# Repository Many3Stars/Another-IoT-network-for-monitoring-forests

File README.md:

# IoT Monitoring System for Forest Environments

Author: Manuel Álvarez Herrera  
Supervisor: José Antonio García Souto  
Year: 2024

## Abstract

This project implements an IoT system to monitor forest environments, particularly coniferous and oak forests, aiming to study the effects of climate change. The IoT network consists of sensor nodes, intermediate nodes, and a database, enabling the collection and analysis of environmental and tree health data.

## Objectives

The primary objective is to observe the impact of climate change on trees by collecting relevant data such as temperature, humidity, solar radiation, and other key indicators.

## Technologies Used

- **Hardware:** Arduino, Raspberry Pi, Dragino NBSN95, LSN50, temperature, humidity sensors, and more.
- **Communication Protocols:** LoRa, NB-IoT, WiFi.
- **Databases:** InfluxDB, ThingsBoard, Home Assistant.
- **Weather Stations:** Ecowitt, Wunderground, Weathercloud.

## IoT Network Structure

1. **Sensor Node A:** Arduino Uno, Raspberry Pi 4 B, sensors for foliage and soil.
2. **Sensor Node B:** Dragino NBSN95 and LSN50 devices.
3. **Sensor Node C:** Sainlogic WS3500 weather station.

## Results

The system was successfully tested in a controlled environment, obtaining accurate data for forest environment analysis. The tests demonstrated the system's viability for monitoring remote forests.

## Conclusion

The designed IoT system is scalable, energy-efficient, and adaptable to various environments, including farms and urban forest areas.

## Repository

The code and additional documentation are available in the following GitHub repository:  
[Another IoT network for monitoring forests](https://github.com/Many3Stars/IoT-network-for-monitoring-forests)

## References

1. K. Raviteja, M. Supriya, "IoT-Based Agriculture Monitoring System", Springer, 2020.
2. N. Suma, S. Samson, "Recent Innovations in Computing and Communication", 2021.
3. Kazuho M., Takeshi O., "Dependence of Stomatal Conductance on Leaf Chlorophyll Concentration", 2025.

---

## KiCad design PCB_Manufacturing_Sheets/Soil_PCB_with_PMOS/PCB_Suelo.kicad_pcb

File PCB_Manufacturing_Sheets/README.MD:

# PCB Manufacturing Sheets

This folder contains all the necessary schematics and designs for the manufacturing of PCBs related to the data acquisition and power supply of soil and leaf sensors.

## Overview

The designs in this folder are intended to be used with KiCad for PCB design and fabrication. The PCBs are categorized into two primary functions:

- **Power Supply PCBs:** Provide the required voltage levels for sensors and associated circuits.
- **Datalog PCBs:** Handle data acquisition from sensors and ensure reliable data transmission to the Arduino for processing.

### Sensors Supported

1. **Soil Sensors:** Measure parameters like soil humidity, temperature, and pH.
2. **Leaf Sensors:** Measure parameters like leaf humidity, temperature, and stomatal temperature.

---

## Components and Design Highlights

### Key Components
- Voltage regulators for stable power supply.
- PMOS/NMOS transistors for energy-efficient activation/deactivation.
- Circuitry for data acquisition and sensor-specific power requirements.

### PMOS vs NMOS Switching
- **PMOS Design (Recommended):** Low leakage current in the "off" state, ensuring better energy efficiency.
- **NMOS Design:** Functional but with higher leakage current, making it less efficient for long-term applications.

---

## Folder Structure and Details

Each subfolder contains files for a specific PCB design:

### 1. **Power_Supply_PCB**
   - Contains the schematic and PCB layout for the power supply.
   - Includes voltage regulation and distribution for all components.

### 2. **Leaf_PCB_with_NMOS**
   - PCB design for leaf sensors using an NMOS transistor for switching.
   - Measures leaf-related parameters like humidity and temperature.

### 3. **Leaf_PCB_with_PMOS**
   - PCB design for leaf sensors using a PMOS transistor for switching.
   - Optimized for energy efficiency with minimal leakage current.

### 4. **Soil_PCB_with_NMOS**
   - PCB design for soil sensors using an NMOS transistor for switching.
   - Measures soil parameters like humidity, temperature, and pH.

### 5. **Soil_PCB_with_PMOS**
   - PCB design for soil sensors using a PMOS transistor for switching.
   - Designed for low-power consumption and long-term deployments.

---

## Design Recommendations

- **Use PMOS designs for both leaf and soil sensors** to minimize power consumption during standby periods.
- Ensure all components are compatible with the specific voltage and current requirements of your sensors.

---

## How to Use

1. Open the KiCad project files from the respective subfolders.
2. Verify the schematic and PCB design as per your requirements.
3. Export the Gerber files for manufacturing.
4. Assemble the PCB using the components listed in the schematic.

---

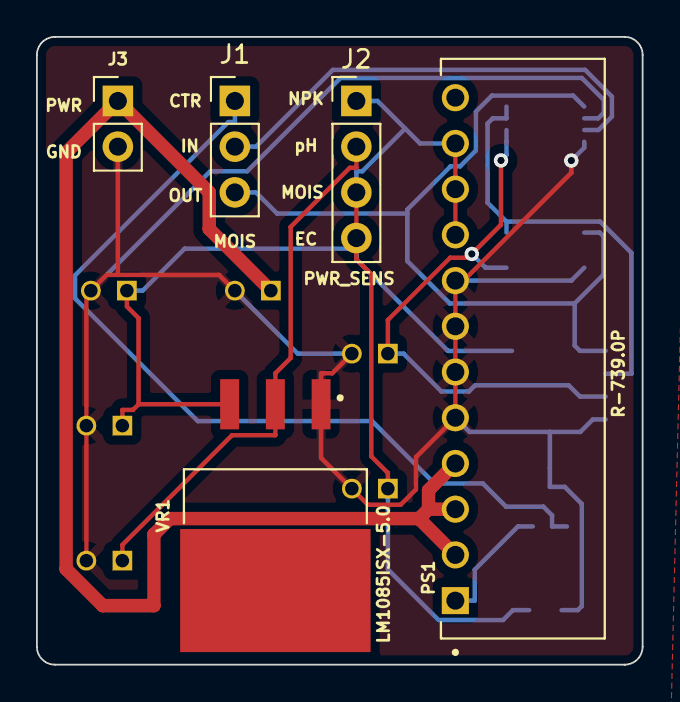
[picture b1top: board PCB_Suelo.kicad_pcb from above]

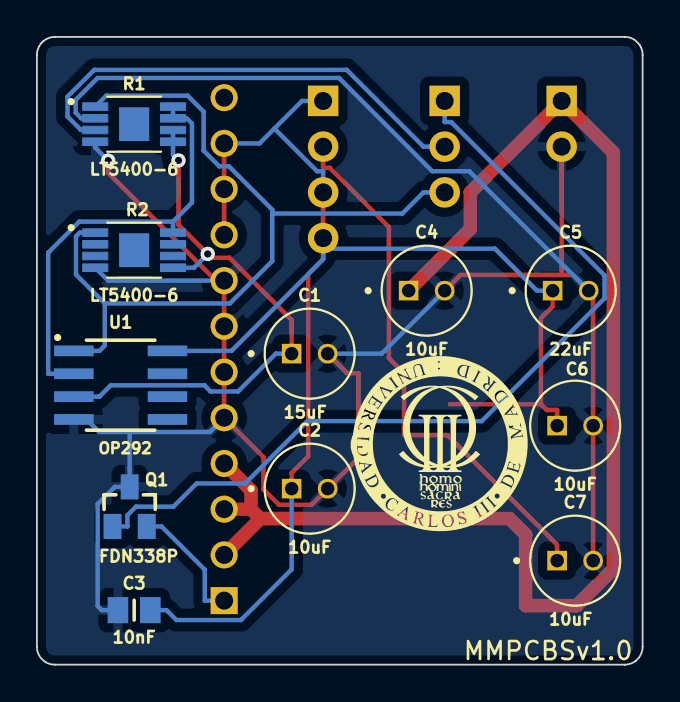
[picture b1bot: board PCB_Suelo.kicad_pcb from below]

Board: 2 copper layers, 33.7 x 34.9 mm, 17 parts (12 on the bottom side), 10 nets.

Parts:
C1, C2, C4, C5, C6, C7: EEUFC1H150; CAPPRD200W50D500H1100
C3: CL21B103KBANNNC; CAPC2012X140N
G: L; Logo2
J1: Conn_01x03; PinHeader_1x03_P2.54mm_Vertical
J2: Conn_01x04; PinHeader_1x04_P2.54mm_Vertical
J3: Conn_01x02; PinHeader_1x02_P2.54mm_Vertical
PS1: R-739.0P; CONV_R-739.0P
Q1: FDN338P; SSOT-3
R1, R2: LT5400BCMS8E-6#PBF; SOP65P490X110-9N
U1: OP292GSZ-REEL; SOIC127P600X175-8N
VR1: LM1085ISX-5.0/NOPB; TO254P1435X464-4N

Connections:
9V: C2.P, C3.2, C5.P, C6.P, J2.1, J2.3, J2.4, PS1.9 (VOUT), PS1.10 (VOUT), PS1.11 (VOUT), U1.8 (V+), VR1.3 (INPUT)
CTR: J1.1, Q1.1
GND: C1.N, C2.N, C3.1, C4.N, C5.N, C6.N, C7.N, J3.2, PS1.5 (GND), PS1.6 (GND), PS1.7 (GND), PS1.8 (GND), Q1.3, R1.2, R1.4, R2.4, U1.4 (V-), VR1.1 (ADJ/GND)
IN_MOISTURE: J1.2, R1.3
unnamed: C1.P, R1.5, R1.6, R2.5, U1.3 (+INA)
unnamed: PS1.1 (~ON/OFF), Q1.2
unnamed: R1.7, R1.8, R2.8, U1.2 (-INA)
OUT_MOISTURE: J1.3, R1.1, R2.1, U1.1 (OUTA)
PWR: C4.P, J3.1, PS1.2 (VIN), PS1.3 (VIN), PS1.4 (VIN)
PWR_pH: C7.P, J2.2, VR1.2 (OUTPUT_2)

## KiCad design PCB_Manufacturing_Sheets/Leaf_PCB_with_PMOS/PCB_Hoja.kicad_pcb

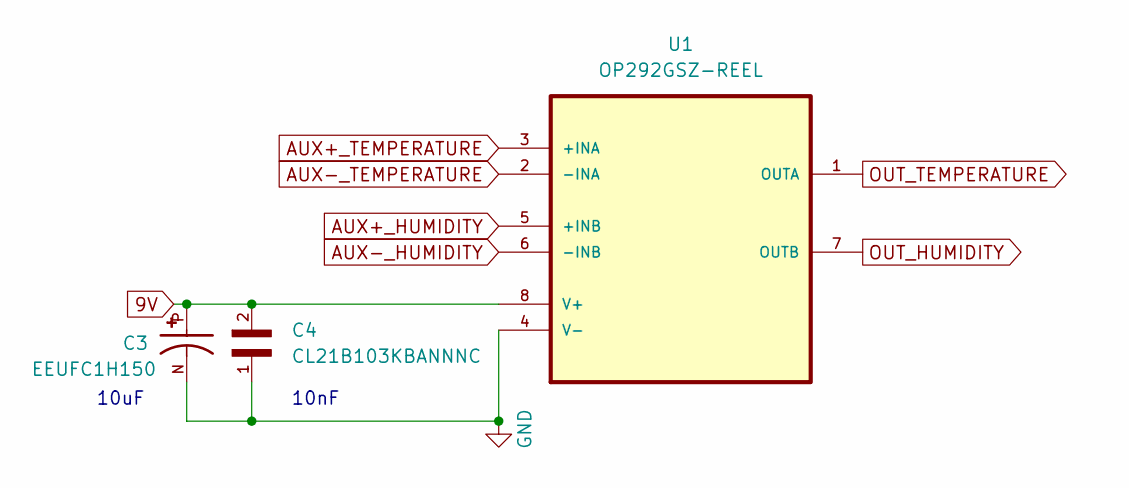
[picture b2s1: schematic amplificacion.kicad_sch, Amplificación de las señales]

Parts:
C3: EEUFC1H150; CAPPRD200W50D500H1100; PARTREV 20-DEC-19
C4: CL21B103KBANNNC; CAPC2012X140N
U1: OP292GSZ-REEL; SOIC127P600X175-8N; MPN OP292GSZ-REEL

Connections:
9V: C3.P, C4.2, U1.8 (V+); also elsewhere on the board
AUX+_HUMIDITY: U1.5 (+INB); also elsewhere on the board
AUX+_TEMPERATURE: U1.3 (+INA); also elsewhere on the board
AUX-_HUMIDITY: U1.6 (-INB); also elsewhere on the board
AUX-_TEMPERATURE: U1.2 (-INA); also elsewhere on the board
GND: C3.N, C4.1, U1.4 (V-); also elsewhere on the board
OUT_HUMIDITY: U1.7 (OUTB); also elsewhere on the board
OUT_TEMPERATURE: U1.1 (OUTA); also elsewhere on the board

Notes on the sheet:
10nF
10uF

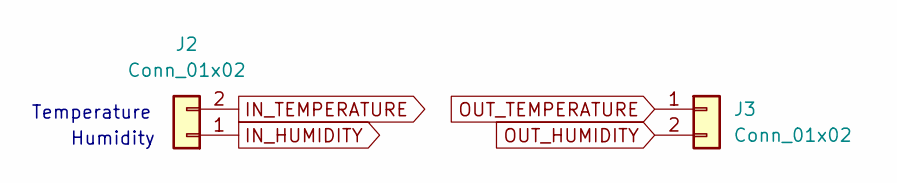
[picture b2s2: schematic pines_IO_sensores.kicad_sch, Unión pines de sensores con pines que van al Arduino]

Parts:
J2, J3: Conn_01x02; PinHeader_1x02_P2.54mm_Vertical

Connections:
IN_HUMIDITY: J2.1; also elsewhere on the board
IN_TEMPERATURE: J2.2; also elsewhere on the board
OUT_HUMIDITY: J3.2; also elsewhere on the board
OUT_TEMPERATURE: J3.1; also elsewhere on the board

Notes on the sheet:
Humidity
Temperature

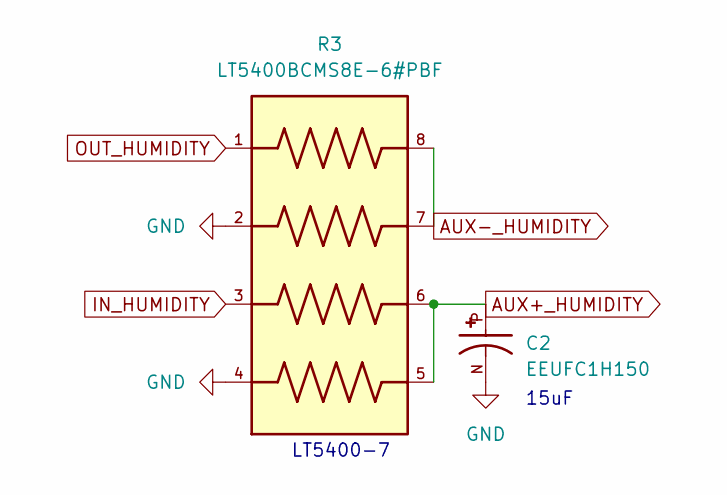
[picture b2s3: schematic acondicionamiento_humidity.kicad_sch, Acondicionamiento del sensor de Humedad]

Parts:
C2: EEUFC1H150; CAPPRD200W50D500H1100; PARTREV 20-DEC-19
R3: LT5400BCMS8E-6#PBF; SOP65P490X110-9N; PARTREV I

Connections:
AUX+_HUMIDITY: C2.P, R3.5, R3.6; also elsewhere on the board
AUX-_HUMIDITY: R3.7, R3.8; also elsewhere on the board
GND: C2.N, R3.2, R3.4; also elsewhere on the board
IN_HUMIDITY: R3.3; also elsewhere on the board
OUT_HUMIDITY: R3.1; also elsewhere on the board

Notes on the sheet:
LT5400-7
15uF

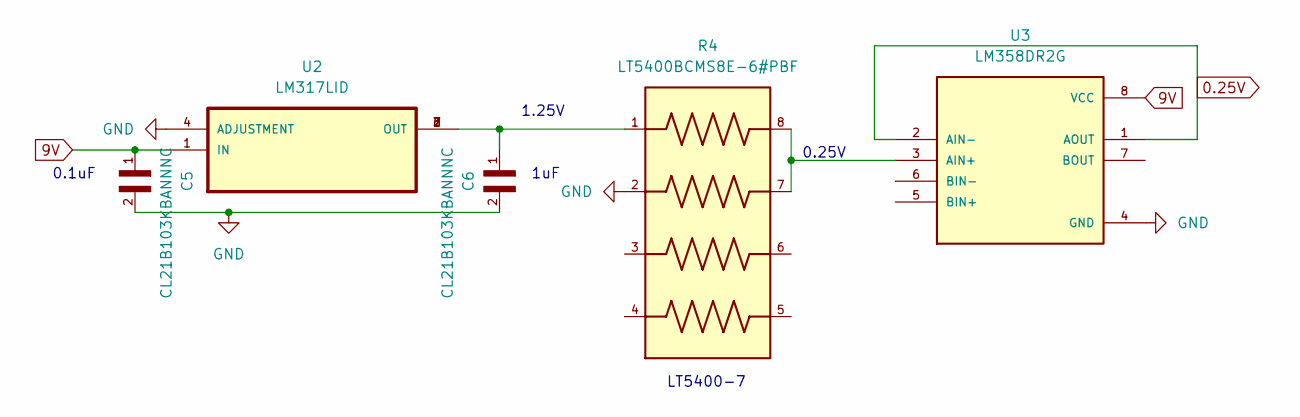
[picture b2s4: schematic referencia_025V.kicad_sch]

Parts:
C5, C6: CL21B103KBANNNC; CAPC2012X140N
R4: LT5400BCMS8E-6#PBF; SOP65P490X110-9N; PARTREV I
U2: LM317LID; SOIC127P599X175-8N
U3: LM358DR2G; SOIC127P600X175-8N

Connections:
0.25V: U3.1 (AOUT), U3.2 (AIN-); also elsewhere on the board
9V: C5.1, U2.1 (IN), U3.8 (VCC); also elsewhere on the board
GND: C5.2, C6.2, R4.2, U2.4 (ADJUSTMENT), U3.4 (GND); also elsewhere on the board
unnamed: C6.1, R4.1, U2.2 (OUT), U2.3 (OUT), U2.6 (OUT), U2.7 (OUT)
unnamed: R4.7, R4.8, U3.3 (AIN+)

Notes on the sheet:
1uF
0.25V
0.1uF
LT5400-7
1.25V

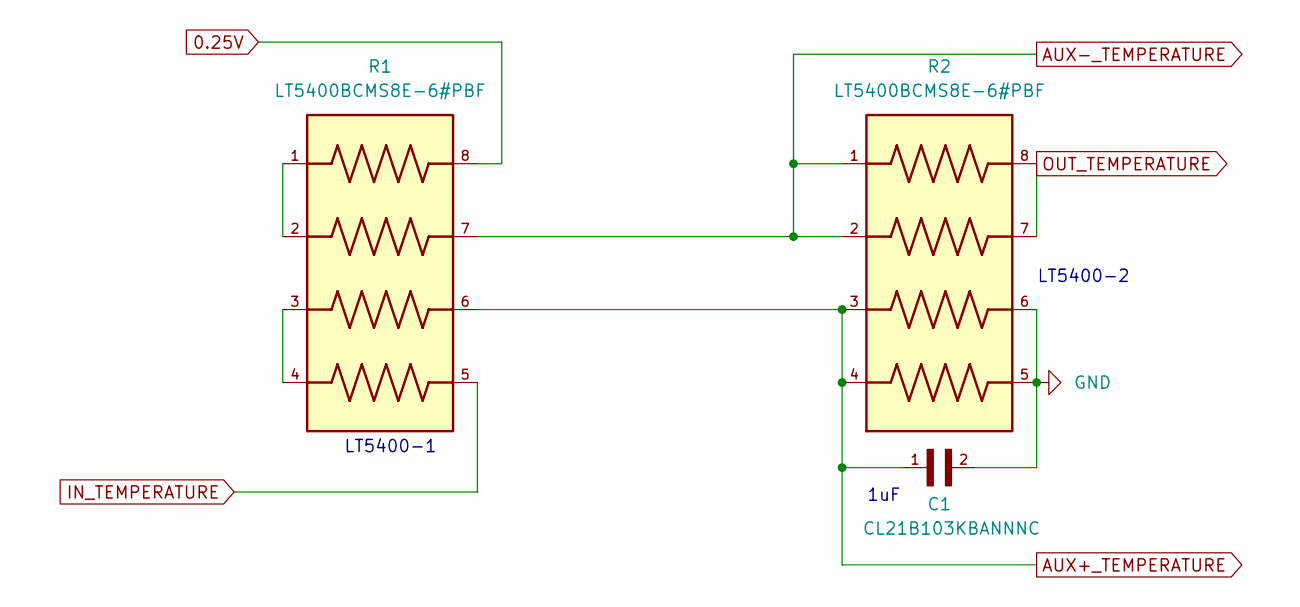
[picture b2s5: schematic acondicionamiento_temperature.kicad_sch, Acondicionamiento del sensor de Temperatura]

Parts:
C1: CL21B103KBANNNC; CAPC2012X140N
R1, R2: LT5400BCMS8E-6#PBF; SOP65P490X110-9N; PARTREV I

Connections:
0.25V: R1.8; also elsewhere on the board
AUX+_TEMPERATURE: C1.1, R1.6, R2.3, R2.4; also elsewhere on the board
AUX-_TEMPERATURE: R1.7, R2.1, R2.2; also elsewhere on the board
GND: C1.2, R2.5, R2.6; also elsewhere on the board
IN_TEMPERATURE: R1.5; also elsewhere on the board
unnamed: R1.1, R1.2
unnamed: R1.3, R1.4
OUT_TEMPERATURE: R2.7, R2.8; also elsewhere on the board

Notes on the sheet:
LT5400-2
LT5400-1
1uF

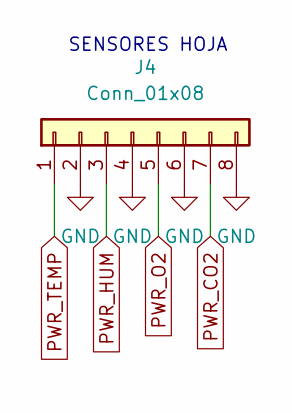
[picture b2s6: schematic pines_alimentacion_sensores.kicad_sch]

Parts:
J4: Conn_01x08; PinHeader_1x08_P2.54mm_Vertical

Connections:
GND: J4.2, J4.4, J4.6, J4.8; also elsewhere on the board
PWR_CO2: J4.3, J4.5, J4.7; also elsewhere on the board
PWR_TEMP: J4.1; also elsewhere on the board

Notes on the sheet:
SENSORES HOJA

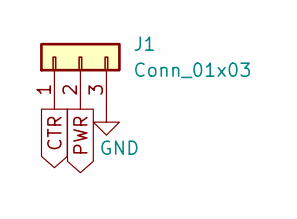
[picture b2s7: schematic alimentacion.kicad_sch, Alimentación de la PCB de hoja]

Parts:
J1: Conn_01x03; PinHeader_1x03_P2.54mm_Vertical

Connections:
CTR: J1.1; also elsewhere on the board
GND: J1.3; also elsewhere on the board
PWR: J1.2; also elsewhere on the board

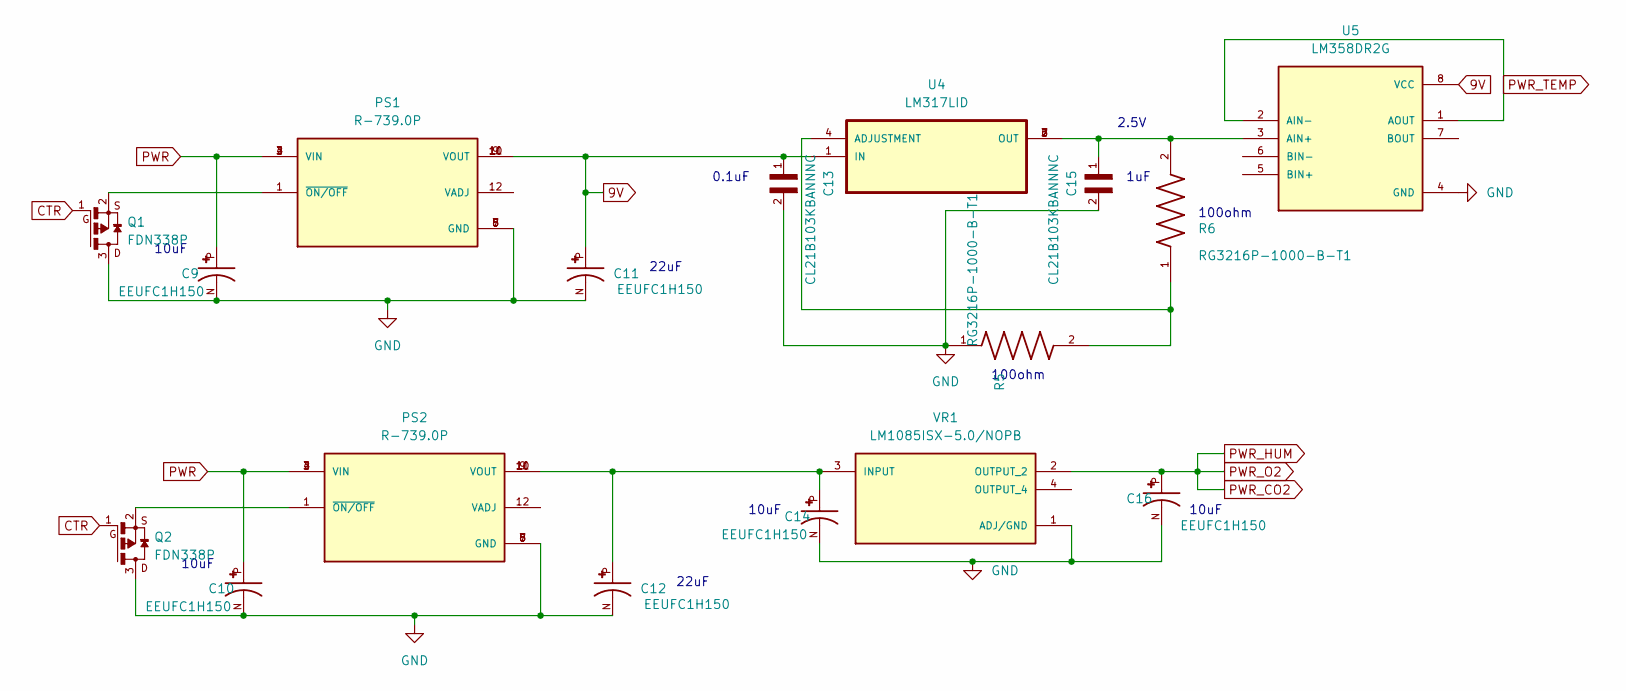
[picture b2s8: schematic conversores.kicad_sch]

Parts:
C9, C10, C11, C12, C14, C16: EEUFC1H150; CAPPRD200W50D500H1100; PARTREV 20-DEC-19
C13, C15: CL21B103KBANNNC; CAPC2012X140N
PS1, PS2: R-739.0P; CONV_R-739.0P; PARTREV 5
Q1, Q2: FDN338P; SSOT-3
R5, R6: RG3216P-1000-B-T1; RESC3216X50N
U4: LM317LID; SOIC127P599X175-8N
U5: LM358DR2G; SOIC127P600X175-8N
VR1: LM1085ISX-5.0/NOPB; TO254P1435X464-4N; PARTREV I

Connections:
9V: C11.P, C13.1, PS1.9 (VOUT), PS1.10 (VOUT), PS1.11 (VOUT), U4.1 (IN), U5.8 (VCC); also elsewhere on the board
CTR: Q1.1, Q2.1; also elsewhere on the board
GND: C9.N, C10.N, C11.N, C12.N, C13.2, C14.N, C15.2, C16.N, PS1.5 (GND), PS1.6 (GND), PS1.7 (GND), PS1.8 (GND), PS2.5 (GND), PS2.6 (GND), PS2.7 (GND), PS2.8 (GND), Q1.3, Q2.3, R5.1, U5.4 (GND), VR1.1 (ADJ/GND); also elsewhere on the board
unnamed: C12.P, C14.P, PS2.9 (VOUT), PS2.10 (VOUT), PS2.11 (VOUT), VR1.3 (INPUT)
unnamed: C15.1, R6.2, U4.2 (OUT), U4.3 (OUT), U4.6 (OUT), U4.7 (OUT), U5.3 (AIN+)
unnamed: PS1.1 (~ON/OFF), Q1.2
unnamed: PS2.1 (~ON/OFF), Q2.2
unnamed: R5.2, R6.1, U4.4 (ADJUSTMENT)
PWR: C9.P, C10.P, PS1.2 (VIN), PS1.3 (VIN), PS1.4 (VIN), PS2.2 (VIN), PS2.3 (VIN), PS2.4 (VIN); also elsewhere on the board
PWR_CO2: C16.P, VR1.2 (OUTPUT_2); also elsewhere on the board
PWR_TEMP: U5.1 (AOUT), U5.2 (AIN-); also elsewhere on the board

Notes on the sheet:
10uF
22uF
1uF
0.1uF
100ohm
2.5V

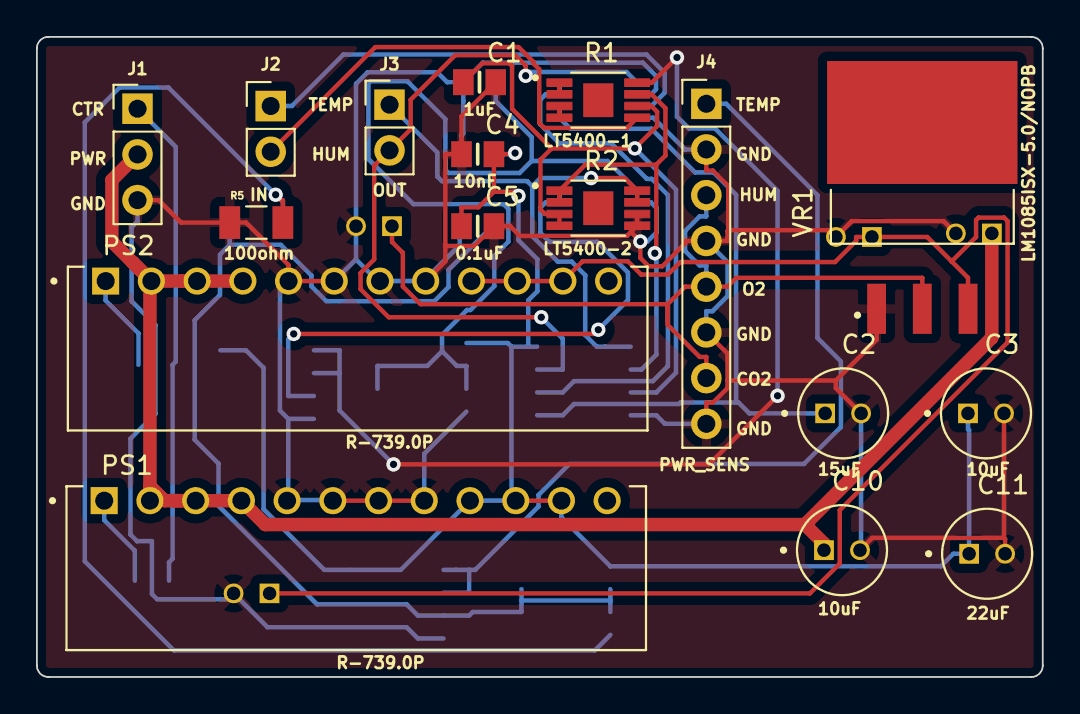
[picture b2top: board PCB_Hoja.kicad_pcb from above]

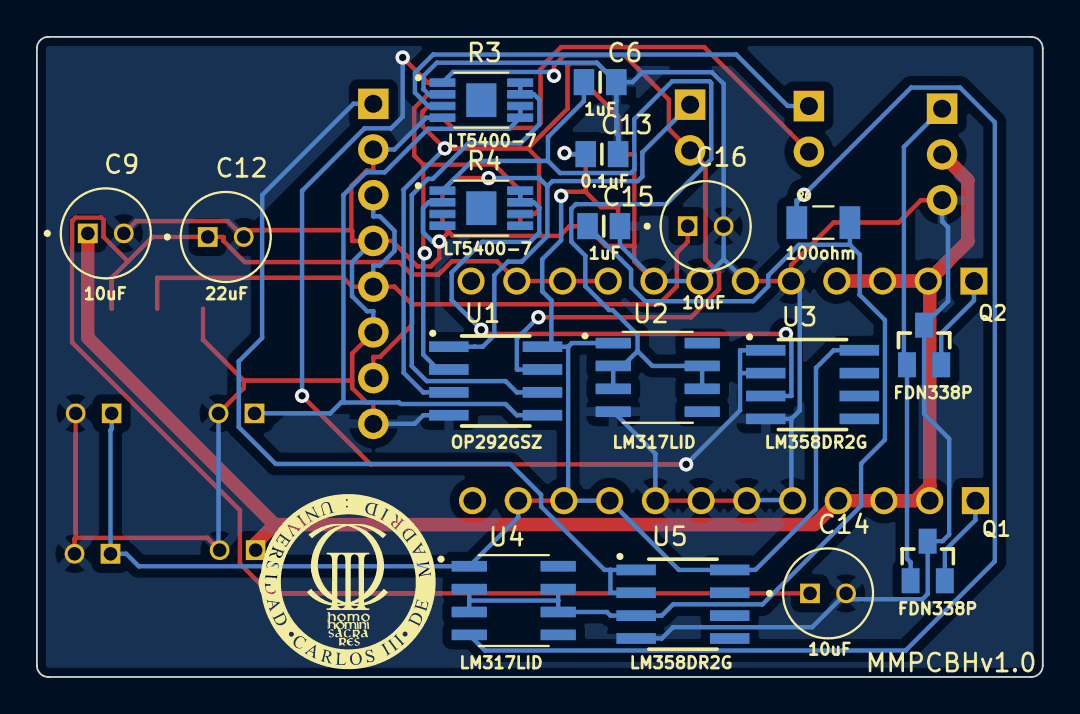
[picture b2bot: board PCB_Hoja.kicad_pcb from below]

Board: 2 copper layers, 55.9 x 35.6 mm, 35 parts (18 on the bottom side), 24 nets.

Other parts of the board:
G: L; Logo2

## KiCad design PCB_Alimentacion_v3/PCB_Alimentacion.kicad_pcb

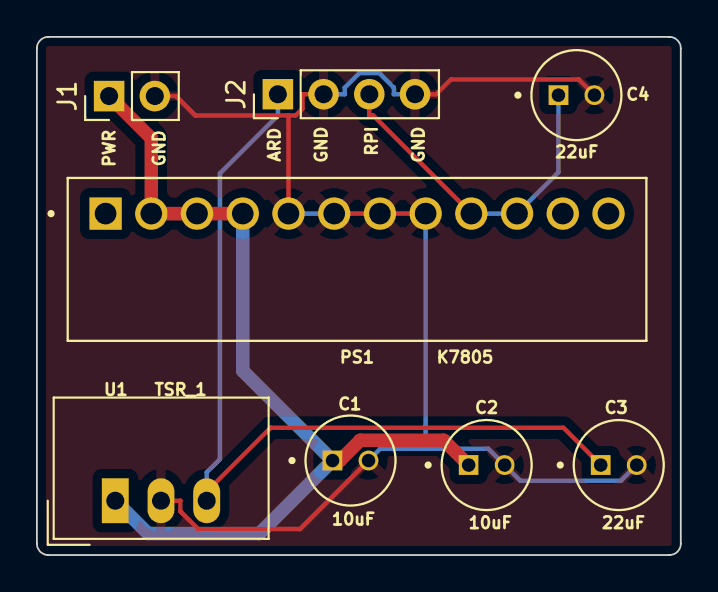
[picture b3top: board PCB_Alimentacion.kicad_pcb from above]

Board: 2 copper layers, 35.8 x 28.8 mm, 9 parts (1 on the bottom side), 4 nets.

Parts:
C1, C2, C3, C4: EEUFC1H150; CAPPRD200W50D500H1100
G: L; Logo2
J1: Conn_01x02; PinHeader_1x02_P2.54mm_Vertical
J2: Conn_01x04; PinHeader_1x04_P2.54mm_Vertical
PS1: K7805-3AR3; CONV_K7805-3AR3
U1: TSR_1-2490; Converter_DCDC_TRACO_TSR-1_THT

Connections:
GND: C1.N, C2.N, C3.N, C4.N, J1.2, J2.2, J2.4, PS1.5 (GND), PS1.6 (GND), PS1.7 (GND), PS1.8 (GND), U1.2 (GND)
PWR: C1.P, C2.P, J1.1, PS1.2 (VIN), PS1.3 (VIN), PS1.4 (VIN), U1.1 (Vin)
PWR_Arduino: C3.P, J2.1, U1.3 (Vout)
PWR_Raspberry: C4.P, J2.3, PS1.9 (+VO1), PS1.10 (+VO1)

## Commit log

2024-12-15 Add Codes
